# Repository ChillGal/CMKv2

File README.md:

Note that this revision of the PCB has a flaw with the pad layout for the neopixels, they are in the wrong orientation.

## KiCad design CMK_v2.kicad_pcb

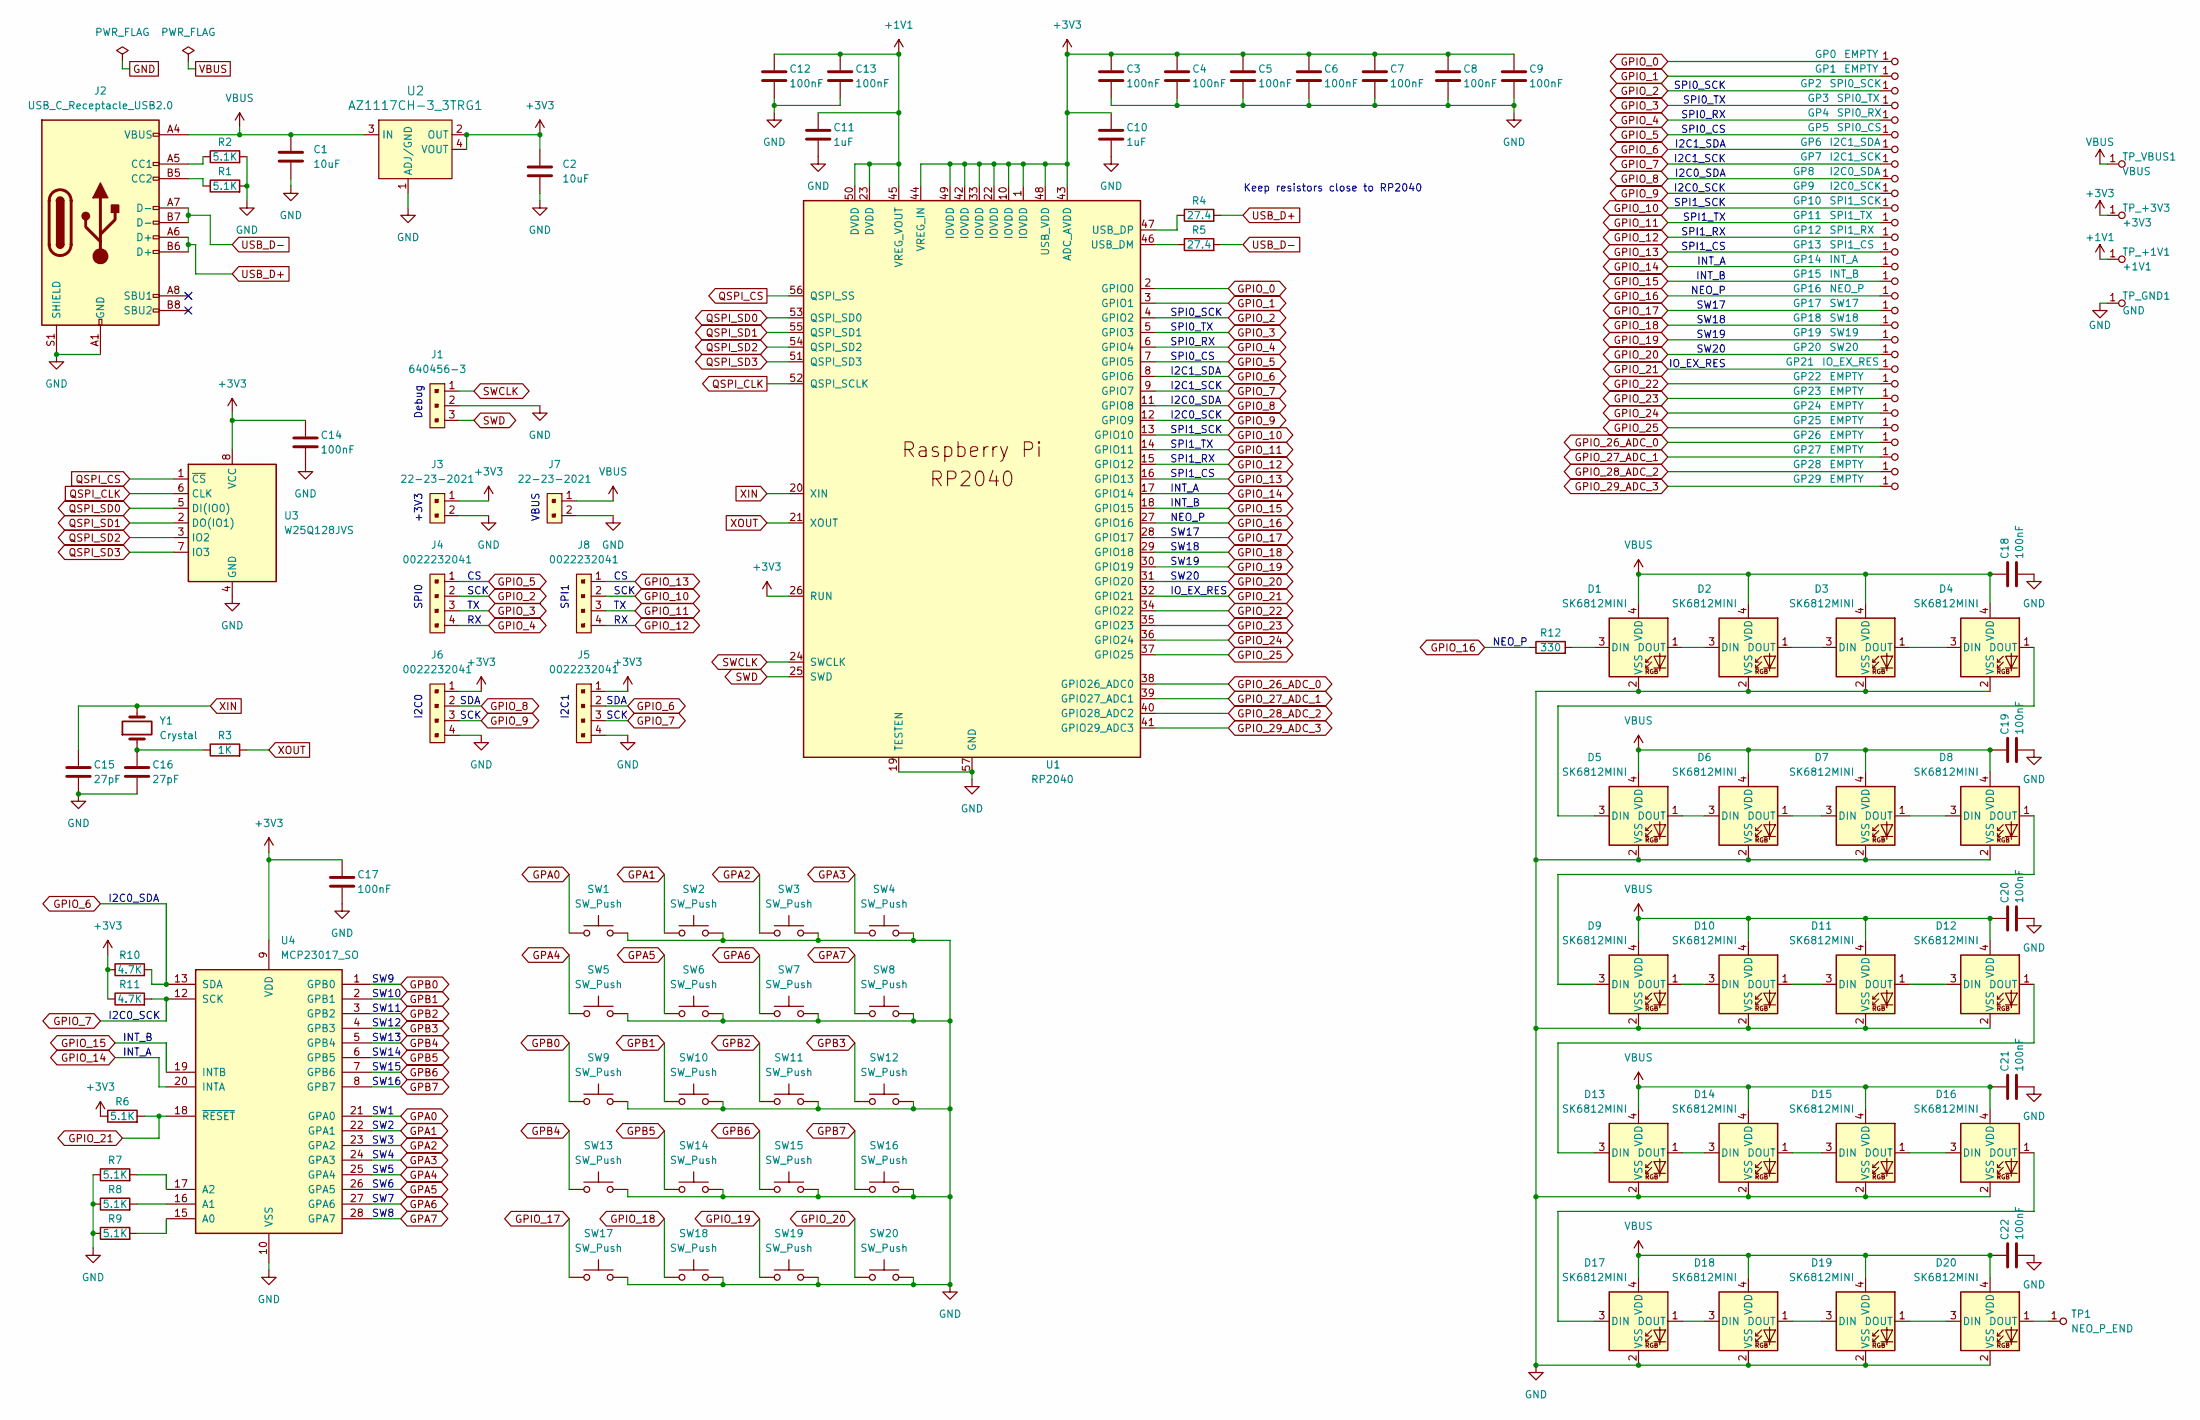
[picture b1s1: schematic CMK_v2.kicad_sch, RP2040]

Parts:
C1, C2: 10uF; C_0603_1608Metric_Pad1.08x0.95mm_HandSolder
C3, C4, C5, C6, C7, C8, C9, C12, C13, C14, C17, C18, C19, C20, C21, C22: 100nF; C_0603_1608Metric_Pad1.08x0.95mm_HandSolder
C10, C11: 1uF; C_0603_1608Metric_Pad1.08x0.95mm_HandSolder
C15, C16: 27pF; C_0603_1608Metric_Pad1.08x0.95mm_HandSolder
D1, D2, D3, D4, D5, D6, D7, D8, D9, D10, D11, D12, D13, D14, D15, D16, D17, D18, D19, D20: SK6812MINI; MX_SK6812MINI-E_REV
GP0, GP1, GP22, GP23, GP24, GP25, GP26, GP27, GP28, GP29: EMPTY; PROBE_PAD_0805; MPN RCT-0C; Digi-Key_PN A106144CT-ND
GP2: SPI0_SCK; PROBE_PAD_0805; MPN RCT-0C; Digi-Key_PN A106144CT-ND
GP3: SPI0_TX; PROBE_PAD_0805; MPN RCT-0C; Digi-Key_PN A106144CT-ND
GP4: SPI0_RX; PROBE_PAD_0805; MPN RCT-0C; Digi-Key_PN A106144CT-ND
GP5: SPI0_CS; PROBE_PAD_0805; MPN RCT-0C; Digi-Key_PN A106144CT-ND
GP6: I2C1_SDA; PROBE_PAD_0805; MPN RCT-0C; Digi-Key_PN A106144CT-ND
GP7: I2C1_SCK; PROBE_PAD_0805; MPN RCT-0C; Digi-Key_PN A106144CT-ND
GP8: I2C0_SDA; PROBE_PAD_0805; MPN RCT-0C; Digi-Key_PN A106144CT-ND
GP9: I2C0_SCK; PROBE_PAD_0805; MPN RCT-0C; Digi-Key_PN A106144CT-ND
GP10: SPI1_SCK; PROBE_PAD_0805; MPN RCT-0C; Digi-Key_PN A106144CT-ND
GP11: SPI1_TX; PROBE_PAD_0805; MPN RCT-0C; Digi-Key_PN A106144CT-ND
GP12: SPI1_RX; PROBE_PAD_0805; MPN RCT-0C; Digi-Key_PN A106144CT-ND
GP13: SPI1_CS; PROBE_PAD_0805; MPN RCT-0C; Digi-Key_PN A106144CT-ND
GP14: INT_A; PROBE_PAD_0805; MPN RCT-0C; Digi-Key_PN A106144CT-ND
GP15: INT_B; PROBE_PAD_0805; MPN RCT-0C; Digi-Key_PN A106144CT-ND
GP16: NEO_P; PROBE_PAD_0805; MPN RCT-0C; Digi-Key_PN A106144CT-ND
GP17: SW17; PROBE_PAD_0805; MPN RCT-0C; Digi-Key_PN A106144CT-ND
GP18: SW18; PROBE_PAD_0805; MPN RCT-0C; Digi-Key_PN A106144CT-ND
GP19: SW19; PROBE_PAD_0805; MPN RCT-0C; Digi-Key_PN A106144CT-ND
GP20: SW20; PROBE_PAD_0805; MPN RCT-0C; Digi-Key_PN A106144CT-ND
GP21: IO_EX_RES; PROBE_PAD_0805; MPN RCT-0C; Digi-Key_PN A106144CT-ND
J1: 640456-3; PinHeader_1x3_P2.54_Drill1.1mm; MPN 640456-3; Digi-Key_PN A19470-ND
J2: USB_C_Receptacle_USB2.0; USB_C_Receptacle_GCT_USB4085
J3, J7: 22-23-2021; PinHeader_1x2_P2.54mm_Drill1.02mm; MPN 22-23-2021; Digi-Key_PN WM4200-ND
J4, J5, J6, J8: 0022232041; PinHeader_1x4_P2.54mm_Drill1.02mm; MPN 0022232041; Digi-Key_PN WM4202-ND
R1, R2, R6, R7, R8, R9: 5.1K; R_0603
R3: 1K; R_0603
R4, R5: 27.4; R_0603
R10, R11: 4.7K; R_0603
R12: 330; R_0603
SW1, SW2, SW3, SW4, SW5, SW6, SW7, SW8, SW9, SW10, SW11, SW12, SW13, SW14, SW15, SW16, SW17, SW18, SW19, SW20: SW_Push; MX-Hotswap-1U
TP1: NEO_P_END; PROBE_PAD_0805; MPN RCT-0C; Digi-Key_PN A106144CT-ND
TP_+1V1: +1V1; PROBE_PAD_0805; MPN RCT-0C; Digi-Key_PN A106144CT-ND
TP_+3V3: +3V3; PROBE_PAD_0805; MPN RCT-0C; Digi-Key_PN A106144CT-ND
TP_GND1: GND; PROBE_PAD_0805; MPN RCT-0C; Digi-Key_PN A106144CT-ND
TP_VBUS1: VBUS; PROBE_PAD_0805; MPN RCT-0C; Digi-Key_PN A106144CT-ND
U1: RP2040; RP2040-QFN-56
U2: AZ1117CH-3_3TRG1; SOT-223; MPN AZ1117CH-3.3TRG1; Digi-Key_PN AZ1117CH-3.3TRG1DICT-ND
U3: W25Q128JVS; SOIC-8_5.23x5.23mm_P1.27mm
U4: MCP23017_SO; SOIC-28W_7.5x17.9mm_P1.27mm
Y1: Crystal; Crystal_SMD_5032-2Pin_5.0x3.2mm_HandSoldering

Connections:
+1V1: C11.1, C12.1, C13.1, TP_+1V1.1, U1.23 (DVDD), U1.45 (VREG_VOUT), U1.50 (DVDD)
+3V3: C2.1, C3.1, C4.1, C5.1, C6.1, C7.1, C8.1, C9.1, C10.1, C14.1, C17.1, J3.1, J5.1, J6.1, R6.1, R10.1, R11.1, TP_+3V3.1, U1.1 (IOVDD), U1.10 (IOVDD), U1.22 (IOVDD), U1.26 (RUN), U1.33 (IOVDD), U1.42 (IOVDD), U1.43 (ADC_AVDD), U1.44 (VREG_IN), U1.48 (USB_VDD), U1.49 (IOVDD), U2.2 (OUT), U2.4 (VOUT), U3.8 (VCC), U4.9 (VDD)
GND: C1.2, C2.2, C3.2, C4.2, C5.2, C6.2, C7.2, C8.2, C9.2, C10.2, C11.2, C12.2, C13.2, C14.2, C15.2, C16.2, C17.2, C18.2, C19.2, C20.2, C21.2, C22.2, D1.2 (VSS), D2.2 (VSS), D3.2 (VSS), D4.2 (VSS), D5.2 (VSS), D6.2 (VSS), D7.2 (VSS), D8.2 (VSS), D9.2 (VSS), D10.2 (VSS), D11.2 (VSS), D12.2 (VSS), D13.2 (VSS), D14.2 (VSS), D15.2 (VSS), D16.2 (VSS), D17.2 (VSS), D18.2 (VSS), D19.2 (VSS), D20.2 (VSS), J1.2, J2.A1 (GND), J2.A12 (GND), J2.B1 (GND), J2.B12 (GND), J2.S1 (SHIELD), J3.2, J5.4, J6.4, J7.2, R1.2, R2.2, R7.1, R8.1, R9.1, SW1.2, SW2.2, SW3.2, SW4.2, SW5.2, SW6.2, SW7.2, SW8.2, SW9.2, SW10.2, SW11.2, SW12.2, SW13.2, SW14.2, SW15.2, SW16.2, SW17.2, SW18.2, SW19.2, SW20.2, TP_GND1.1, U1.19 (TESTEN), U1.57 (GND), U2.1 (ADJ/GND), U3.4 (GND), U4.10 (VSS)
GPA0: SW1.1, U4.21 (GPA0)
GPA1: SW2.1, U4.22 (GPA1)
GPA2: SW3.1, U4.23 (GPA2)
GPA3: SW4.1, U4.24 (GPA3)
GPA4: SW5.1, U4.25 (GPA4)
GPA5: SW6.1, U4.26 (GPA5)
GPA6: SW7.1, U4.27 (GPA6)
GPA7: SW8.1, U4.28 (GPA7)
GPB0: SW9.1, U4.1 (GPB0)
GPB1: SW10.1, U4.2 (GPB1)
GPB2: SW11.1, U4.3 (GPB2)
GPB3: SW12.1, U4.4 (GPB3)
GPB4: SW13.1, U4.5 (GPB4)
GPB5: SW14.1, U4.6 (GPB5)
GPB6: SW15.1, U4.7 (GPB6)
GPB7: SW16.1, U4.8 (GPB7)
GPIO_0: GP0.1, U1.2 (GPIO0)
GPIO_1: GP1.1, U1.3 (GPIO1)
GPIO_2: GP2.1, J4.2, U1.4 (GPIO2)
GPIO_3: GP3.1, J4.3, U1.5 (GPIO3)
GPIO_4: GP4.1, J4.4, U1.6 (GPIO4)
GPIO_5: GP5.1, J4.1, U1.7 (GPIO5)
GPIO_6: GP6.1, J5.2, R10.2, U1.8 (GPIO6), U4.13 (SDA)
GPIO_7: GP7.1, J5.3, R11.2, U1.9 (GPIO7), U4.12 (SCK)
GPIO_8: GP8.1, J6.2, U1.11 (GPIO8)
GPIO_9: GP9.1, J6.3, U1.12 (GPIO9)
GPIO_10: GP10.1, J8.2, U1.13 (GPIO10)
GPIO_11: GP11.1, J8.3, U1.14 (GPIO11)
GPIO_12: GP12.1, J8.4, U1.15 (GPIO12)
GPIO_13: GP13.1, J8.1, U1.16 (GPIO13)
GPIO_14: GP14.1, U1.17 (GPIO14), U4.20 (INTA)
GPIO_15: GP15.1, U1.18 (GPIO15), U4.19 (INTB)
GPIO_16: GP16.1, R12.1, U1.27 (GPIO16)
GPIO_17: GP17.1, SW17.1, U1.28 (GPIO17)
GPIO_18: GP18.1, SW18.1, U1.29 (GPIO18)
GPIO_19: GP19.1, SW19.1, U1.30 (GPIO19)
GPIO_20: GP20.1, SW20.1, U1.31 (GPIO20)
GPIO_21: GP21.1, R6.2, U1.32 (GPIO21), U4.18 (~RESET)
GPIO_22: GP22.1, U1.34 (GPIO22)
GPIO_23: GP23.1, U1.35 (GPIO23)
GPIO_24: GP24.1, U1.36 (GPIO24)
GPIO_25: GP25.1, U1.37 (GPIO25)
GPIO_26_ADC_0: GP26.1, U1.38 (GPIO26_ADC0)
GPIO_27_ADC_1: GP27.1, U1.39 (GPIO27_ADC1)
GPIO_28_ADC_2: GP28.1, U1.40 (GPIO28_ADC2)
GPIO_29_ADC_3: GP29.1, U1.41 (GPIO29_ADC3)
unnamed: C16.1, R3.1, Y1.1
unnamed: D1.3 (DIN), R12.2
unnamed: D1.1 (DOUT), D2.3 (DIN)
unnamed: D2.1 (DOUT), D3.3 (DIN)
unnamed: D3.1 (DOUT), D4.3 (DIN)
unnamed: D4.1 (DOUT), D5.3 (DIN)
unnamed: D5.1 (DOUT), D6.3 (DIN)
unnamed: D6.1 (DOUT), D7.3 (DIN)
unnamed: D7.1 (DOUT), D8.3 (DIN)
unnamed: D8.1 (DOUT), D9.3 (DIN)
unnamed: D9.1 (DOUT), D10.3 (DIN)
unnamed: D10.1 (DOUT), D11.3 (DIN)
unnamed: D11.1 (DOUT), D12.3 (DIN)
unnamed: D12.1 (DOUT), D13.3 (DIN)
unnamed: D13.1 (DOUT), D14.3 (DIN)
unnamed: D14.1 (DOUT), D15.3 (DIN)
unnamed: D15.1 (DOUT), D16.3 (DIN)
unnamed: D16.1 (DOUT), D17.3 (DIN)
unnamed: D17.1 (DOUT), D18.3 (DIN)
unnamed: D18.1 (DOUT), D19.3 (DIN)
unnamed: D19.1 (DOUT), D20.3 (DIN)
unnamed 70: D20.1 (DOUT), TP1.1; also elsewhere on the board
unnamed: J2.A5 (CC1), R2.1
unnamed: J2.B5 (CC2), R1.1
unnamed: R5.1, U1.46 (USB_DM)
unnamed: R4.1, U1.47 (USB_DP)
unnamed: R9.2, U4.15 (A0)
unnamed: R8.2, U4.16 (A1)
unnamed: R7.2, U4.17 (A2)
QSPI_CLK: U1.52 (QSPI_SCLK), U3.6 (CLK)
QSPI_CS: U1.56 (QSPI_SS), U3.1 (~CS)
QSPI_SD0: U1.53 (QSPI_SD0), U3.5 (DI(IO0))
QSPI_SD1: U1.55 (QSPI_SD1), U3.2 (DO(IO1))
QSPI_SD2: U1.54 (QSPI_SD2), U3.3 (IO2)
QSPI_SD3: U1.51 (QSPI_SD3), U3.7 (IO3)
SWCLK: J1.1, U1.24 (SWCLK)
SWD: J1.3, U1.25 (SWD)
USB_D+: J2.A6 (D+), J2.B6 (D+), R4.2
USB_D-: J2.A7 (D-), J2.B7 (D-), R5.2
VBUS: C1.1, C18.1, C19.1, C20.1, C21.1, C22.1, D1.4 (VDD), D2.4 (VDD), D3.4 (VDD), D4.4 (VDD), D5.4 (VDD), D6.4 (VDD), D7.4 (VDD), D8.4 (VDD), D9.4 (VDD), D10.4 (VDD), D11.4 (VDD), D12.4 (VDD), D13.4 (VDD), D14.4 (VDD), D15.4 (VDD), D16.4 (VDD), D17.4 (VDD), D18.4 (VDD), D19.4 (VDD), D20.4 (VDD), J2.A4 (VBUS), J2.A9 (VBUS), J2.B4 (VBUS), J2.B9 (VBUS), J7.1, TP_VBUS1.1, U2.3 (IN)
XIN: C15.1, U1.20 (XIN), Y1.2
XOUT: R3.2, U1.21 (XOUT)

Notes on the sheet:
SW8
SPI1_RX
I2C0_SDA
I2C0_SCK
SW4
I2C1_SCK
SPI1_CS
INT_A
IO_EX_RES
Keep resistors close to RP2040
SW10
SW15
SCK
SPI0_CS
SW17
SPI1_SCK
SW6
INT_B
NEO_P
VBUS
SW18
SW16
SPI0
SPI0_RX
SW13
SW20
SW7
SDA
SW9
SPI0_SCK
SW2
SW14
I2C0
SW19
SW5
I2C1_SDA
SW1
SPI1_TX
SW11
SCK

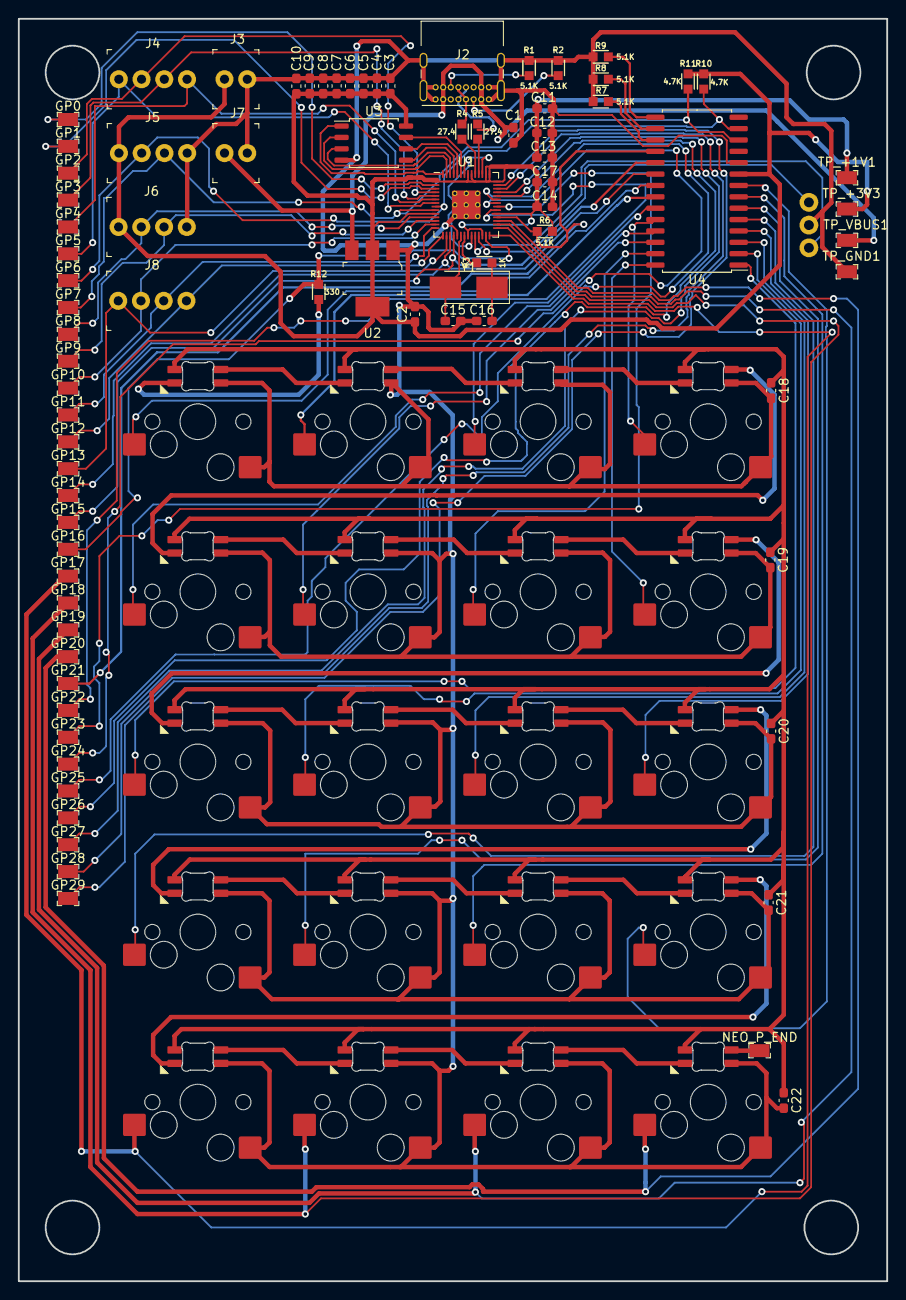
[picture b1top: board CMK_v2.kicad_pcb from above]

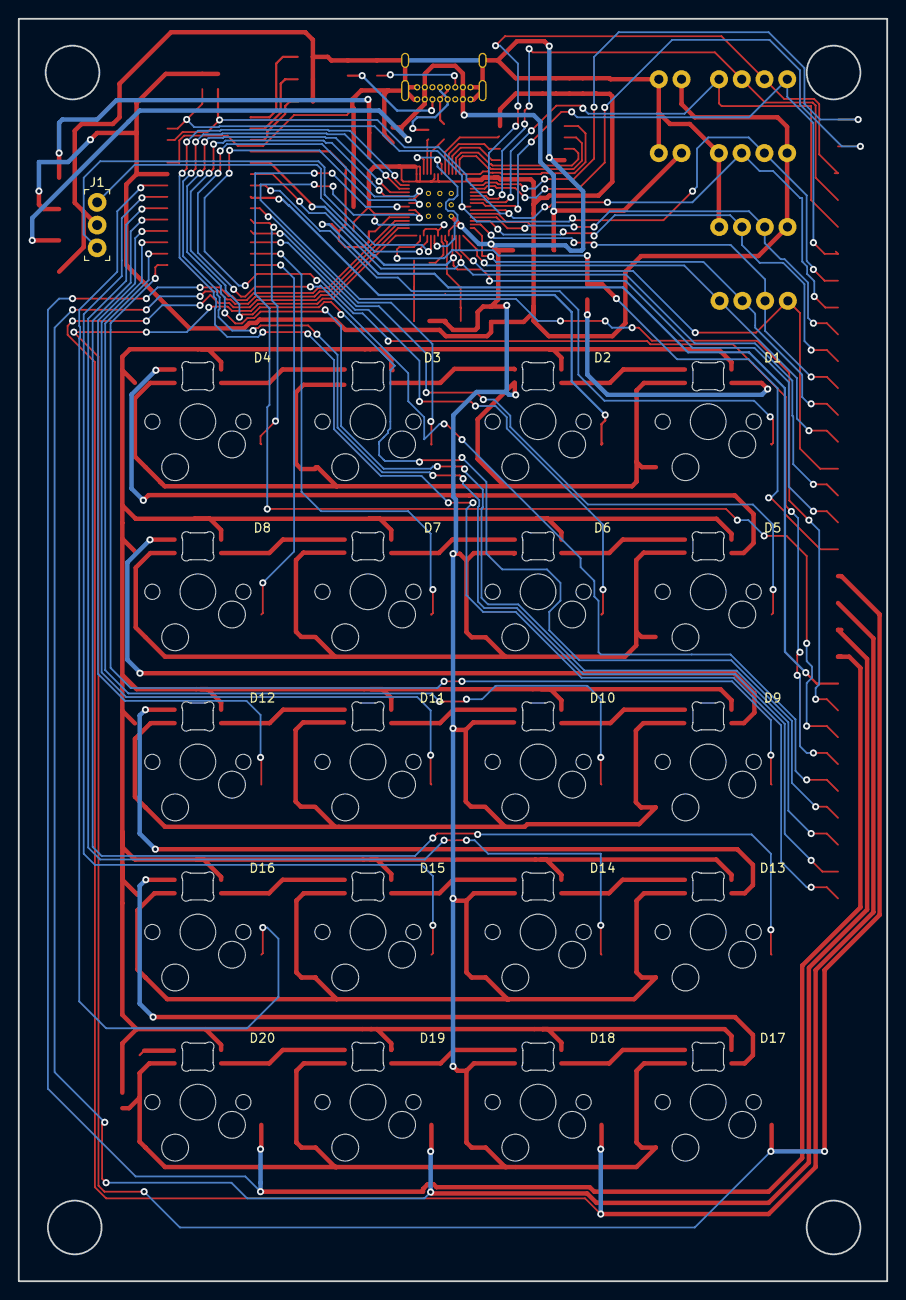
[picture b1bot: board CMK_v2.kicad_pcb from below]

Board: 2 copper layers, 97.0 x 141.0 mm, 122 parts (41 on the bottom side), 91 nets.

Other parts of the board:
NEO_P_END: NEO_P_END; PROBE_PAD_0805

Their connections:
unnamed 70: NEO_P_END.1; also elsewhere on the board

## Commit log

2023-08-24 add initial PCB Files + PDFs
